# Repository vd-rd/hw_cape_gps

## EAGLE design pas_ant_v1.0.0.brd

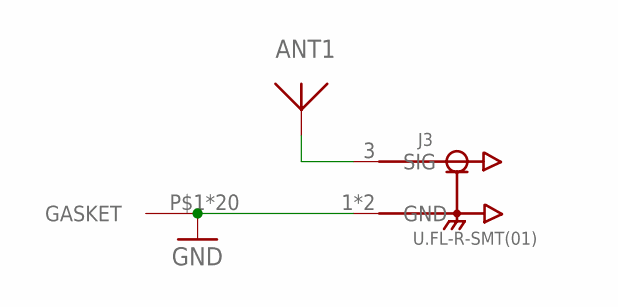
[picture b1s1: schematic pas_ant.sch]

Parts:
ANT1: ANT1590-2540A; 2540A
J3: U.FL-R-SMT(01); HRS_U.FL-R-SMT(01)
U$1: 2118718-2; 2118717-2

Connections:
GND2: J3.1 (GND), J3.2 (GND), U$1.P$1, U$1.P$2, U$1.P$3, U$1.P$4, U$1.P$5, U$1.P$6, U$1.P$7, U$1.P$8, U$1.P$9, U$1.P$10, U$1.P$11, U$1.P$12, U$1.P$13, U$1.P$14, U$1.P$15, U$1.P$16, U$1.P$17, U$1.P$18, U$1.P$19, U$1.P$20
unnamed: ANT1.P$1, J3.3 (SIG)

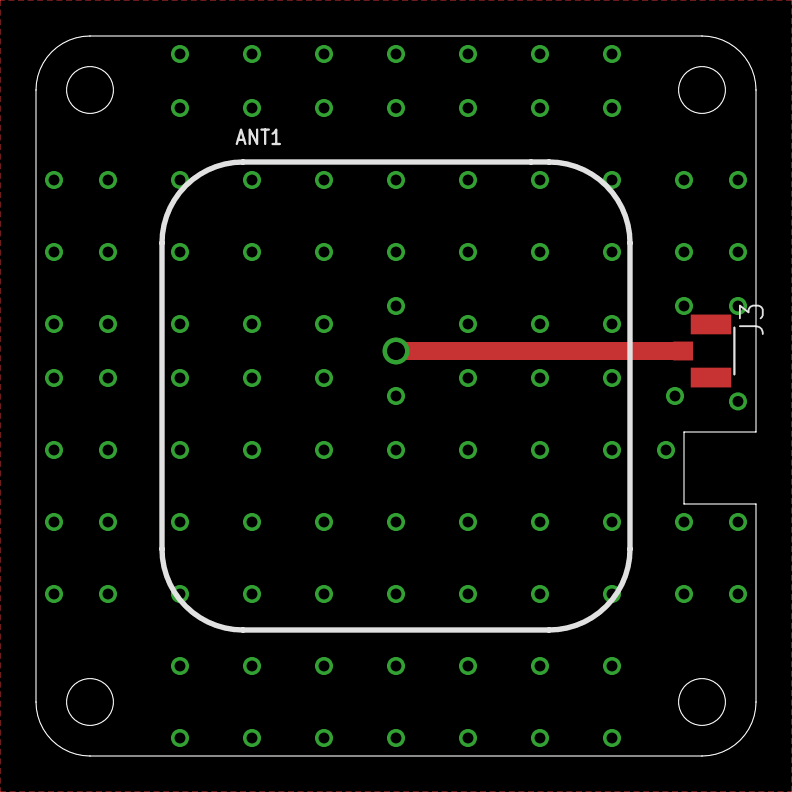
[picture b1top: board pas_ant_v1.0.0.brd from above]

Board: 2 copper layers, 40.0 x 40.0 mm, 3 parts (1 on the bottom side), 2 nets.
